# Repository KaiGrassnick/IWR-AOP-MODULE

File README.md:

# IWR-AOP-MODULE

**Revision 1.1** · KiCad 10 · six-layer, 85.6 × 33.7 mm · designed and simulated, not yet built

A self-contained 60 GHz mmWave radar module built around TI's **IWR6843AOP** (antenna-on-package). It boots its own firmware from on-board flash and connects to a PC over USB-C or a carrier through two rear sockets.

## Features

- **Radar.** IWR6843AOP: 60–64 GHz FMCW, 4 GHz continuous sweep, 3 transmitters and 4 receivers with antennas in the package, C674x DSP, hardware FFT/CFAR accelerator and Arm Cortex-R4F. Detection and tracking run on the radar; the host receives results.
- **Standalone boot.** 32 Mbit QSPI flash (`U301`, MX25L3233F).
- **USB-C.** One cable supplies power and two CP2105 serial ports: control/flashing and radar data. BOOT and RESET buttons select flashing mode.
- **Carrier.** 5 V input, UART and SPI, boot-mode select, reset, disable, interrupt, hardware frame-start pulse and frame-sync input.
- **Power.** USB-C or carrier 5 V feeds an ideal-diode OR and four-rail TI LP87524J-Q1 PMIC. The PMIC sequences the rails and regulates the 1.0 V and 1.8 V rails at the radar (remote sense). A small heat sink on the back under the radar carries the heat away. A TPS386000 supervisor holds the radar in reset until all four rails are good, and the PMIC asserts reset when the carrier disables them. The radar can reach the PMIC over I²C.
- **Debug.** Rear Cortex-10 JTAG header for development off a carrier (Black Magic Probe or XDS110), debug-boot solder jumper, and test pads for every rail, enable and reset. Flashing requires only USB and the BOOT/RESET buttons.
- **RF-ready layout.** The radar sits on the bottom edge with a notch above it, giving the 0.2 mm antenna edge gaps TI specifies. A GND pad sits under the die on both faces.

## Key specifications

| | |
|---|---|
| Supply | 5 V (4.5–5.5 V), ≥ 1.5 A source. Design estimate: about 1.2–1.3 A peak, 0.3–0.45 A average |
| USB | USB-C, default USB power (no PD), CP2105 dual UART |
| Carrier logic | 3.3 V, not 5 V tolerant |
| Carrier sockets | `J400` 2×6 (UART, control, 5 V in) and `J401` 2×5 (SPI, data); HCTL PM254, 2.54 mm, 8.5 mm |
| Mounting | Three M3 holes |
| Board | 85.6 × 33.7 mm, 6 layers, 1.6 mm, ENIG, filled and capped vias |
| Parts | 164 assembled on 46 BOM lines, both sides (`R604` and `C605` left unfitted), plus a 14 × 14 × 6 mm heat sink bonded on by hand |
| Ambient | Up to about 58 °C at 1.75 W radar power and 43 °C at 2.3 W in still air with the heat sink (model, spec §10). Target: 30 °C room temperature; in a case, the case decides the margin ([`case/`](case/README.md)) |

Full modes, rails, boot, mechanics, stackup and firmware requirements: **[hardware specification](docs/STG-HW-SPEC-004_IWR-AOP-MODULE.md)**. Enclosure design: [case notes](case/README.md).

## Using it

Use USB-C or a carrier, never both: they share the radar's control UART.

### USB-C

Power from a USB-C port or charger offering at least 1.5 A (default USB power, no PD). USB-A-to-C cables and 500/900 mA ports can brown out during chirps. The CP2105 bridge enumerates as two COM ports:

| Channel | COM port | Radar side | Direction | Use |
|---|---|---|---|---|
| Control | *Enhanced* (ECI) | UARTA | Both | Commands, configuration, UART flashing |
| Data | *Standard* (SCI) | UARTB TX | Radar → PC | Data stream |

| Action | How |
|---|---|
| Reset | Press RESET |
| Flash | Hold RESET, hold BOOT, release RESET, release BOOT; program over the Enhanced port; press RESET to boot from flash |
| JTAG | `J301` Cortex-10 header (1.27 mm); bridge `JP300` for debug boot (spec §4.3) |

### Carrier

Power from one regulated 5 V supply (4.5–5.5 V, ≥ 1.5 A) on `J400.11/.12`, with USB unplugged. All logic is 3.3 V and not 5 V tolerant. A carrier can talk to the radar three ways:

| Channel | Radar side | Pins | Direction | Use |
|---|---|---|---|---|
| Control UART | UARTA | TX `J400.1`, RX `J400.2` | Both | Commands, configuration, UART flashing (same UART as the USB Enhanced port) |
| Data UART | UARTB TX | `J401.9` | Radar → carrier | Data stream (same as the USB Standard port) |
| SPI | SPIA, radar is peripheral | CLK `J401.1`, MOSI `J401.3`, MISO `J401.4`, CS `J401.5`; IRQ `J401.7` | Both | Protocol set by the radar firmware |

Control and timing signals:

| Signal | Pin | Direction | Function |
|---|---|---|---|
| `HOST_NRESET` | `J400.8` | Open-drain, both | Pull low to reset. High means rails good and reset released |
| `HOST_DISABLE` | `J400.7` | In, active high | High turns off every radar rail |
| `AOP_SOP2` | `J400.5` | In | Boot select: high during reset enters UART flashing |
| `AOP_NERROR_OUT` | `J400.6` | Out, open-drain | Radar error flag (optional) |
| `HOST_SYNC_IN` | `J400.3` | In | Frame trigger, 25 ns–4 µs pulse (optional) |
| `FRAME_START` | `J401.8` | Out | Frame-start pulse (optional) |

To flash from a carrier: hold `J400.5` high, pulse `J400.8` low, program over the control UART, release `J400.5` and reset again.

Carrier rules (spec §5):

- Keep every carrier output and pull-up high-impedance until `J400.8` first goes high, and while `HOST_DISABLE` is asserted.
- Reset only by pulling `J400.8` low open-drain; never drive it high.

## Pinout

Back view: `J400` is on the left and `J401` on the right.

Full pin directions and carrier rules: spec §5.

## Mechanical

Back view, mm. Everything is symmetric about the board centrelines (℄). Sockets sit on the hole columns, centred vertically. Keep carrier metal out of the antenna aperture (spec §6). For CAD work use the board STEP, [`docs/3d/IWR-AOP-MODULE.step`](docs/3d/IWR-AOP-MODULE.step) (origin at the outline's top-left corner); window and heat-path rules for a case are in [`case/`](case/README.md).

## Cost

Parts for one board cost about $37.60 at LCSC list prices for a single board and $33.10 each for 30 (15 November 2026); the IWR6843AOP is about $19.50 of that. Per-part prices are in [docs/bom-cost.csv](docs/bom-cost.csv), rebuilt by `tools/bom_cost.py`. The bare PCB, JLCPCB's assembly fees and the heat sink (bought separately, a few dollars) come on top; JLCPCB quotes those at order time.

## Repository layout

```
IWR-AOP-MODULE.kicad_pro / .kicad_sch / .kicad_pcb / .kicad_dru   KiCad 10 project, design rules
IWR-AOP-MODULE.kicad_sch   Power entry, LM66200 source OR, enable, integration notes
rails.kicad_sch        LP87524J-Q1 PMIC, four radar rails, reset, test pads
aop.kicad_sch          IWR6843AOP, crystal, boot flash, straps, JTAG
interfaces.kicad_sch   USB-C, CP2105 dual UART, J400 / J401 sockets, buttons
libraries/             Project symbols, footprints and STEP 3D models (IWR-AOP-MODULE.*)
                       Sockets, JTAG header, buttons and LP87524J: LCSC/EasyEDA models fitted
                       to the pads; U200: KiCad's 4x4 QFN-24 model
docs/                  Hardware specification and BOM cost
  images/              Board renders, orbit GIF, pinout.svg and dimensions.svg
  videos/              IWR-AOP-MODULE-orbit.mp4
  3d/                  Board STEP (origin: outline top-left)
tools/
  board_svg.py         Pinout and dimension SVG generation
  render/              Blender product renders and orbit video pipeline
  rev11/               Scripts that generate the schematic and layout changes of revision 1.1
  bom_cost.py          Rebuilds docs/bom-cost.csv from current LCSC prices
  heatsink_model.py    STEP model of heat sink HS300 (CadQuery)
simulation/            Netlist checks, post-layout extraction, ngspice and thermal models, results
cosim/                 Firmware running on a model of the board, chirp load replayed in ngspice
manufacturing/         JLCPCB package builder and output (jlcpcb/)
case/                  Notes for the enclosure design: heat path, antenna window, geometry
references/            Datasheets and JLC's sample BOM format
CHANGELOG.md           Release history
LICENSE                MIT license
build/                 Generated outputs (gitignored)
```

The project is self-contained: everything outside the stock KiCad 10 libraries is in `libraries/`.

## Status

**Designed and simulated, not yet built.** The board is fully routed. ERC has no errors; DRC reports 0 unconnected and 0 schematic-parity issues, plus 53 accepted findings (spec §7.3). Post-layout extraction and simulation cover rail voltages at the radar balls, sequencing and reset, loop stability, chirp load steps, ripple, USB hot plug and temperature: see [`simulation/`](simulation/README.md). Test firmware runs on a model of the board in [`cosim/`](cosim/README.md): power-up, flashing, resets, the PMIC trim over I²C (limited to 1000–1005 mV), a thermal governor that throttles from 90 °C and stops at 100 °C, and host settings with compiled-in limits. Three TX in one chirp is off by default because it does not fit the 1.0 V window in the replay. Enclosure requirements (heat path, antenna window, keep-outs) are in [`case/`](case/README.md). Operating conditions and the basis of the models are in spec §10 and the measurements for the first boards in spec §9.

## License

MIT — see [LICENSE](LICENSE).

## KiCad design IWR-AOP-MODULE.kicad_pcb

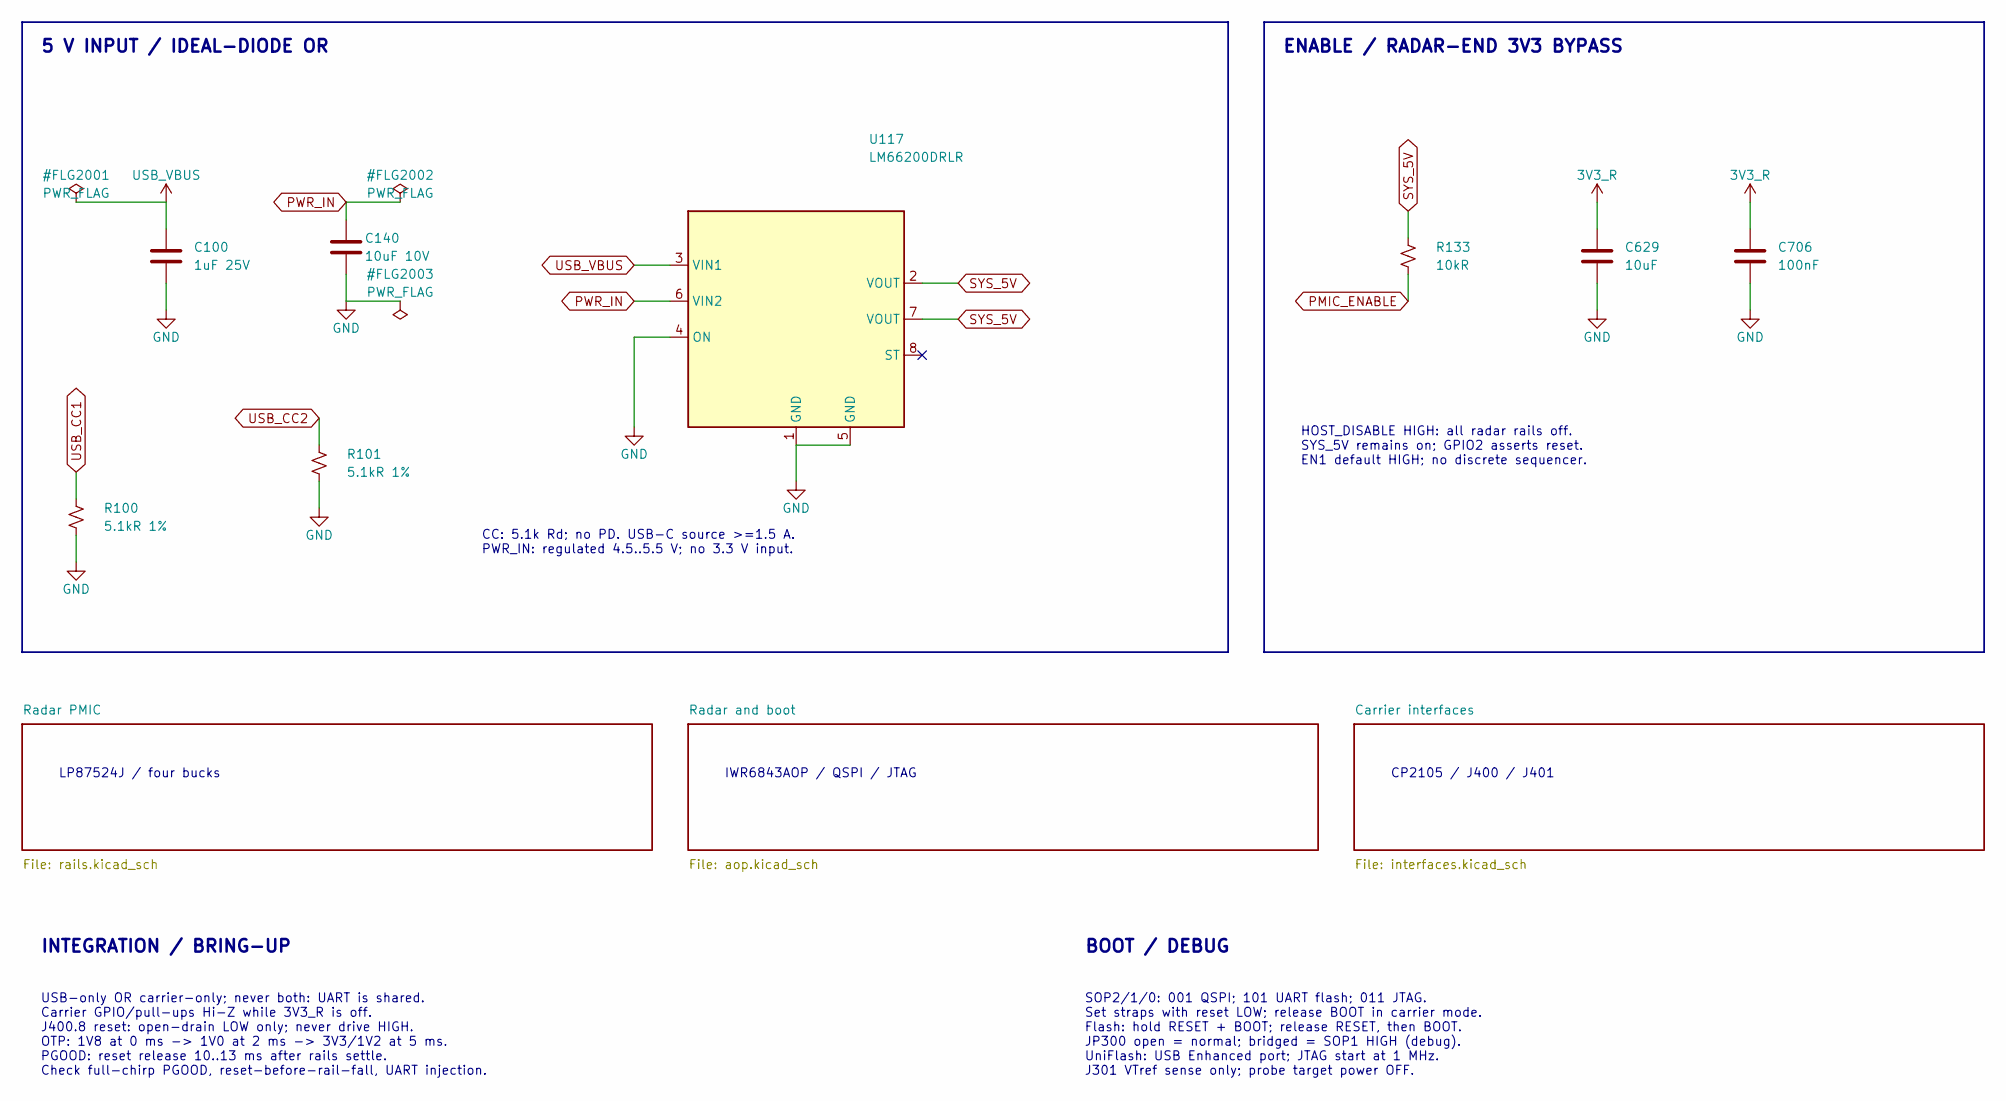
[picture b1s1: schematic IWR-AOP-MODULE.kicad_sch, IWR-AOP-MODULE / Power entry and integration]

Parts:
C100: 1uF 25V; C_0805_2012Metric; MPN CL21B105KBFNNNE; LCSC C28323
C140: 10uF 10V; C_0805_2012Metric; MPN GRM21BR71A106KE51L; LCSC C86038
C629: 10uF; C_0805_2012Metric; Tolerance 10%; Rating X7R 10V; MPN GRM21BR71A106KE51L; LCSC C86038
C706: 100nF; C_0402_1005Metric; MPN CL05B104KO5NNNC; LCSC C1525
R100, R101: 5.1kR 1%; R_0402_1005Metric; MPN 0402WGF5101TCE; LCSC C25905
R133: 10kR; R_0402_1005Metric; MPN 0402WGF1002TCE; LCSC C25744
U117: LM66200DRLR; SOT-583-8; MPN LM66200DRLR; LCSC C3235556

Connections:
3V3_R: C629.1, C706.1; also elsewhere on the board
GND: C100.2, C140.2, C629.2, C706.2, R100.2, R101.2, U117.1 (GND), U117.4 (ON), U117.5 (GND); also elsewhere on the board
PMIC_ENABLE: R133.2; also elsewhere on the board
PWR_IN: C140.1, U117.6 (VIN2); also elsewhere on the board
SYS_5V: R133.1, U117.2 (VOUT), U117.7 (VOUT); also elsewhere on the board
USB_CC1: R100.1; also elsewhere on the board
USB_CC2: R101.1; also elsewhere on the board
USB_VBUS: C100.1, U117.3 (VIN1); also elsewhere on the board

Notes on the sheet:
5 V INPUT / IDEAL-DIODE OR
CC: 5.1k Rd; no PD. USB-C source >=1.5 A. PWR_IN: regulated 4.5..5.5 V; no 3.3 V input.
ENABLE / RADAR-END 3V3 BYPASS
HOST_DISABLE HIGH: all radar rails off. SYS_5V remains on; GPIO2 asserts reset. EN1 default HIGH; no discrete sequencer.
LP87524J / four bucks
IWR6843AOP / QSPI / JTAG
CP2105 / J400 / J401
INTEGRATION / BRING-UP
USB-only OR carrier-only; never both: UART is shared. Carrier GPIO/pull-ups Hi-Z while 3V3_R is off. J400.8 reset: open-drain LOW only; never drive HIGH. OTP: 1V8 at 0 ms -> 1V0 at 2 ms -> 3V3/1V2 at 5 ms. PGOOD: reset release 10..13 ms after rails settle. Check full-chirp PGOOD, reset-before-rail-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
BOOT / DEBUG
SOP2/1/0: 001 QSPI; 101 UART flash; 011 JTAG. Set straps with reset LOW; release BOOT in carrier mode. Flash: hold RESET + BOOT; release RESET, then BOOT. JP300 open = normal; bridged = SOP1 HIGH (debug). UniFlash: USB Enhanced port; JTAG start at 1 MHz. J301 VTref sense only; probe target power OF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

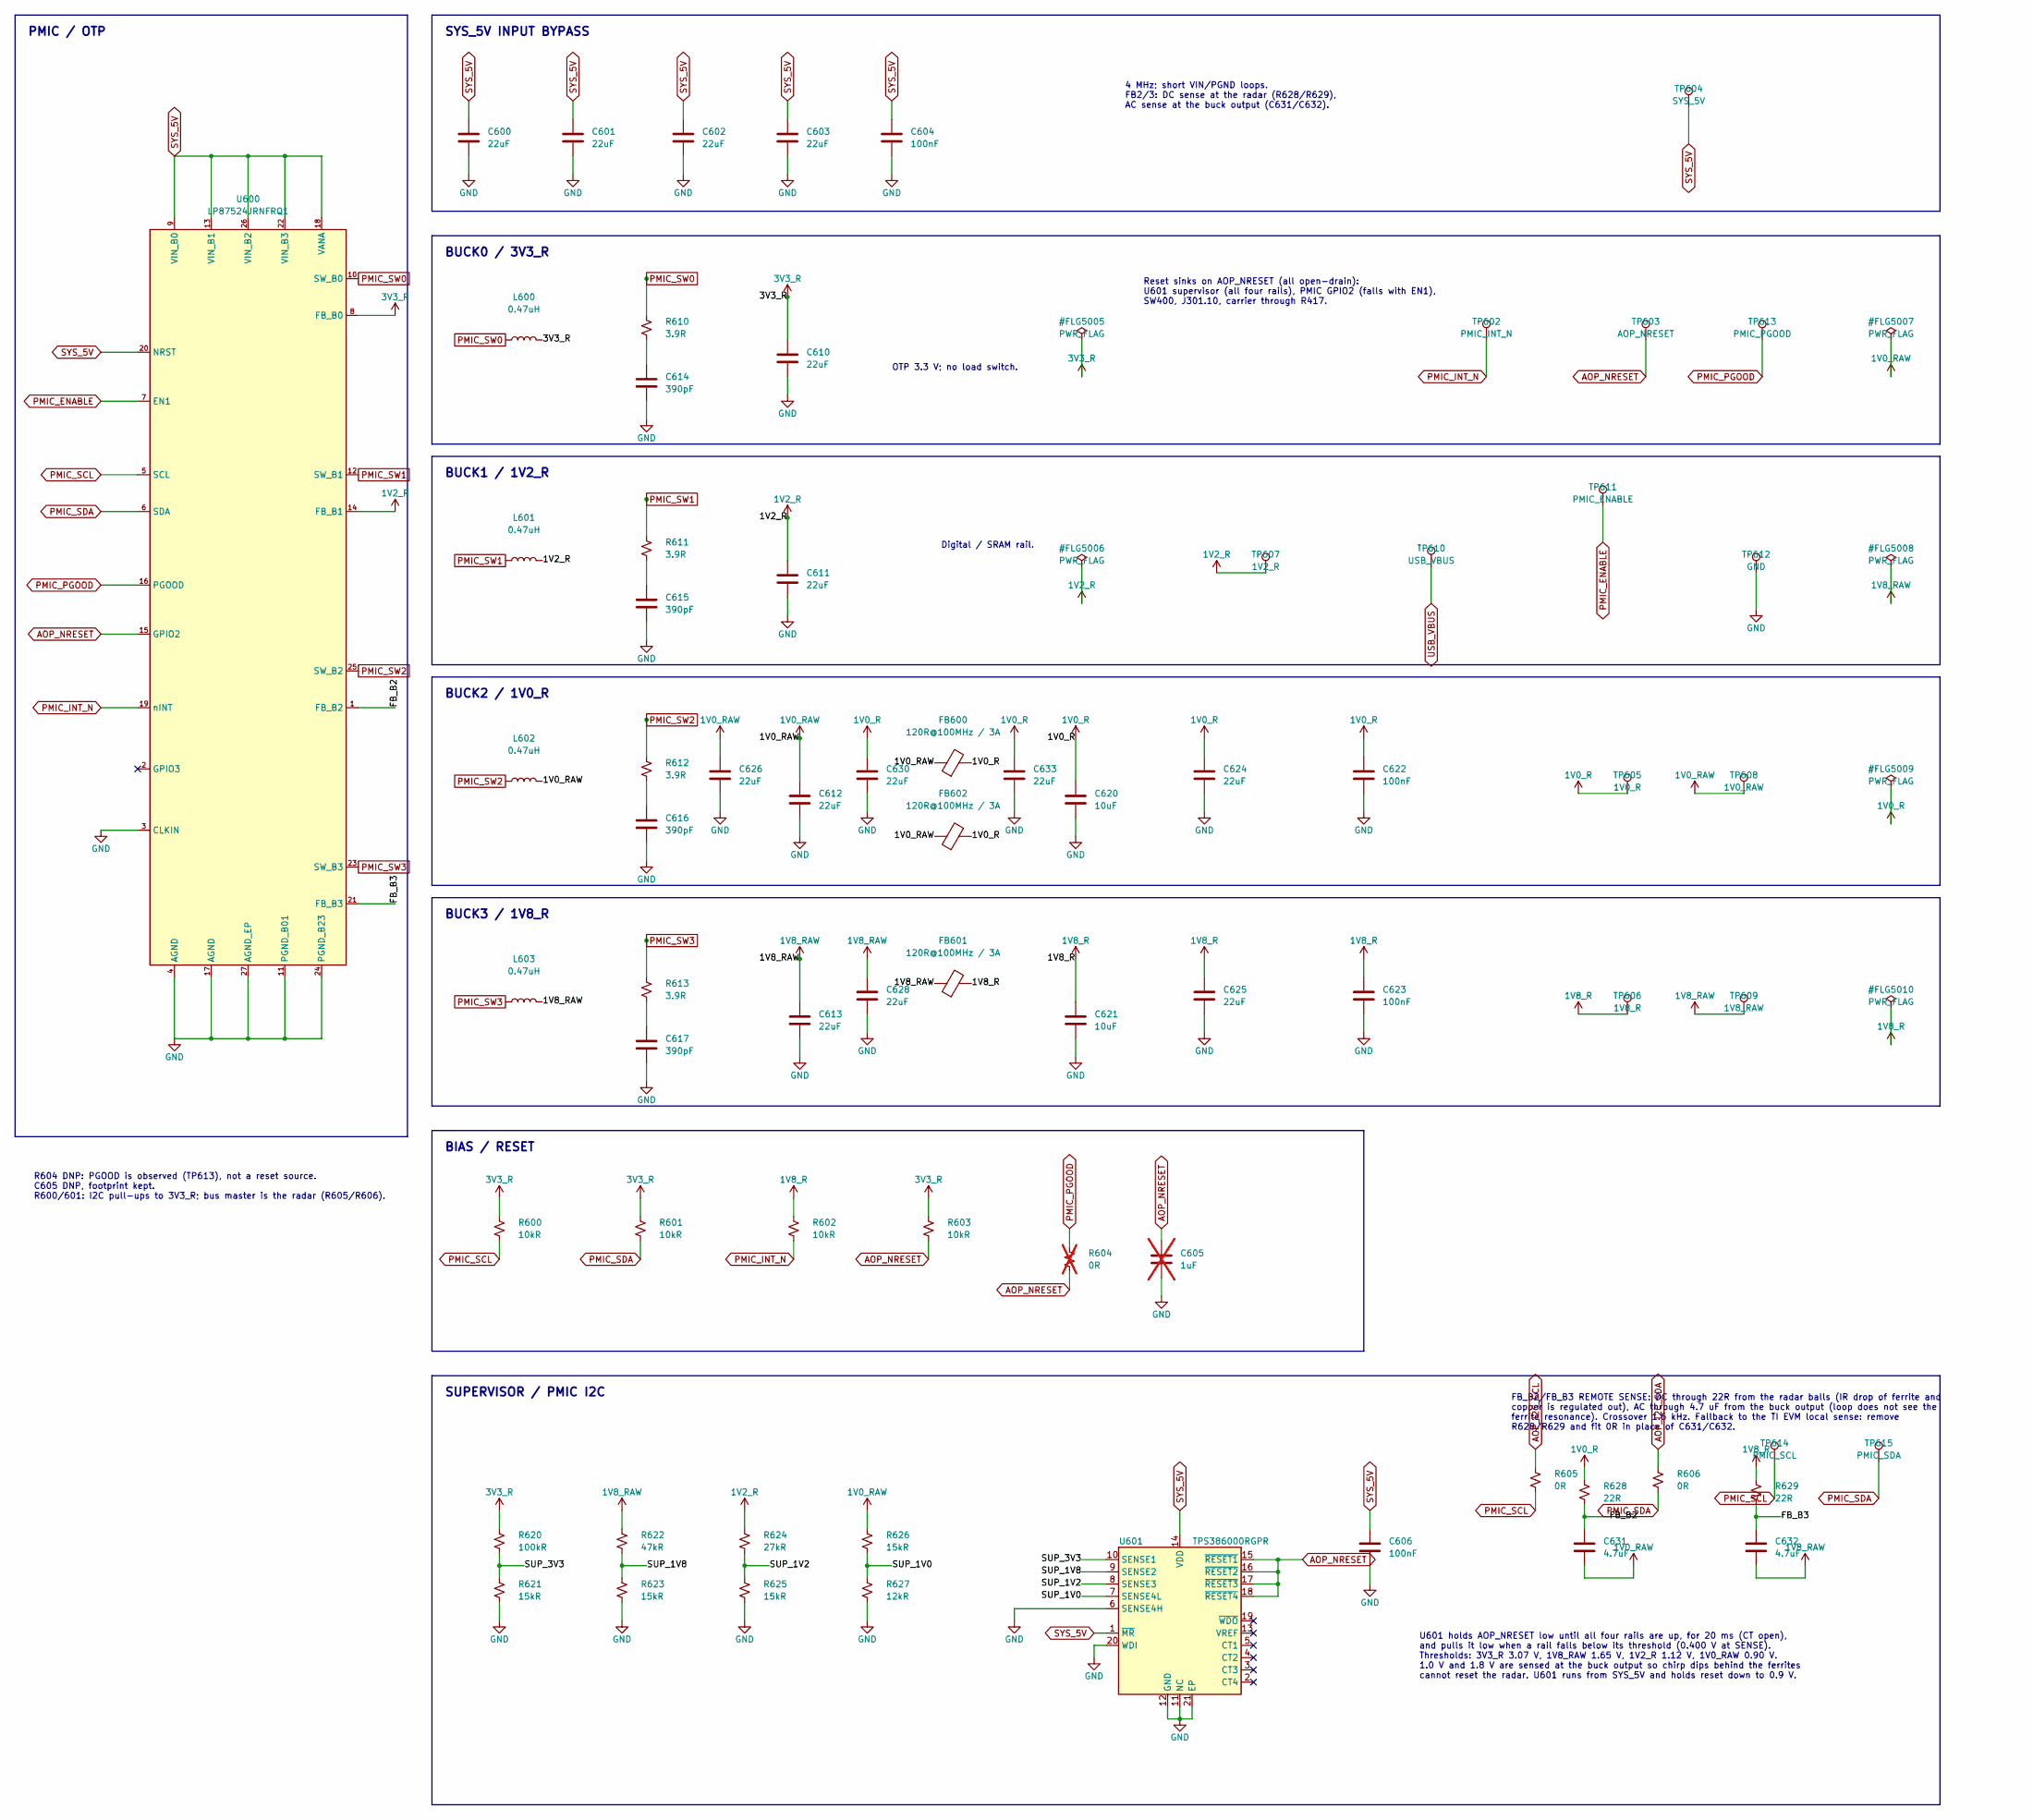
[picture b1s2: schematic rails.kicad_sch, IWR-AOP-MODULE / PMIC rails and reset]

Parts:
C600, C601, C602, C603, C610, C611, C612, C613: 22uF; C_1210_3225Metric; Rating X7R 25V; Tolerance 10%; MPN GRM32ER71E226KE15L; LCSC C21397
C604, C606, C622, C623: 100nF; C_0402_1005Metric; MPN CL05B104KO5NNNC; LCSC C1525
C605: 1uF; C_0603_1608Metric; MPN CL10A105KB8NNNC; LCSC C15849; not fitted
C614, C615, C616, C617: 390pF; C_0402_1005Metric; Tolerance 5%; Rating C0G 50V; MPN GRM1555C1H391JA01D; LCSC C76967
C620, C621: 10uF; C_0805_2012Metric; Tolerance 10%; Rating X7R 10V; MPN GRM21BR71A106KE51L; LCSC C86038
C624, C625, C626, C628, C630, C633: 22uF; C_0805_2012Metric; Rating X5R 25V; Tolerance 20%; MPN CL21A226MAQNNNE; LCSC C45783
C631, C632: 4.7uF; C_0603_1608Metric; Rating X5R 16V; MPN CL10A475KO8NNNC; LCSC C19666
FB600, FB601, FB602: 120R@100MHz / 3A; L_0603_1608Metric; MPN BLM18KG121TH1D; LCSC C437404
L600, L601, L602, L603: 0.47uH; L_Sunlord_MWSA0402S; MPN MWSA0402S-R47MT; LCSC C6331050
R600, R601, R602, R603: 10kR; R_0402_1005Metric; MPN 0402WGF1002TCE; LCSC C25744
R604: 0R; R_0402_1005Metric; MPN 0402WGF0000TCE; LCSC C17168; not fitted
R605, R606: 0R; R_0402_1005Metric; MPN 0402WGF0000TCE; LCSC C17168
R610, R611, R612, R613: 3.9R; R_0603_1608Metric; Tolerance 1%; Rating 100mW; MPN RC0603FR-073R9L; LCSC C482845
R620: 100kR; R_0402_1005Metric; MPN 0402WGF1003TCE; LCSC C25741
R621, R623, R625, R626: 15kR; R_0402_1005Metric; MPN 0402WGF1502TCE; LCSC C25756
R622: 47kR; R_0402_1005Metric; MPN 0402WGF4702TCE; LCSC C25792
R624: 27kR; R_0402_1005Metric; MPN 0402WGF2702TCE; LCSC C25771
R627: 12kR; R_0402_1005Metric; MPN 0402WGF1202TCE; LCSC C25752
R628, R629: 22R; R_0402_1005Metric; MPN 0402WGF220JTCE; LCSC C25092
TP602: PMIC_INT_N; TestPoint_Pad_D1.0mm; MPN PCB_TEST_PAD_1MM
TP603: AOP_NRESET; TestPoint_Pad_D1.0mm; MPN PCB_TEST_PAD_1MM
TP604: SYS_5V; TestPoint_Pad_D1.0mm; MPN PCB_TEST_PAD_1MM
TP605: 1V0_R; TestPoint_Pad_D1.0mm; MPN PCB_TEST_PAD_1MM
TP606: 1V8_R; TestPoint_Pad_D1.0mm; MPN PCB_TEST_PAD_1MM
TP607: 1V2_R; TestPoint_Pad_D1.0mm; MPN PCB_TEST_PAD_1MM
TP608: 1V0_RAW; TestPoint_Pad_D1.0mm; MPN PCB_TEST_PAD_1MM
TP609: 1V8_RAW; TestPoint_Pad_D1.0mm; MPN PCB_TEST_PAD_1MM
TP610: USB_VBUS; TestPoint_Pad_D1.0mm; MPN PCB_TEST_PAD_1MM
TP611: PMIC_ENABLE; TestPoint_Pad_D1.0mm; MPN PCB_TEST_PAD_1MM
TP612: GND; TestPoint_Pad_D1.0mm; MPN PCB_TEST_PAD_1MM
TP613: PMIC_PGOOD; TestPoint_Pad_D1.0mm; MPN PCB_TEST_PAD_1MM
TP614: PMIC_SCL; TestPoint_Pad_D1.0mm; MPN PCB_TEST_PAD_1MM
TP615: PMIC_SDA; TestPoint_Pad_D1.0mm; MPN PCB_TEST_PAD_1MM
U600: LP87524JRNFRQ1; Texas_RNF0026C_LP87524J; MPN LP87524JRNFRQ1; LCSC C701982
U601: TPS386000RGPR; Texas_RGP0020D_VQFN-20-1EP_4x4mm_P0.5mm_EP2.7x2.7mm; MPN TPS386000RGPR; LCSC C702221

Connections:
1V0_R: C620.1, C622.1, C624.1, C630.1, C633.1, FB600.2, FB602.2, R628.1, TP605.1; also elsewhere on the board
1V0_RAW: C612.1, C626.1, C631.2, FB600.1, FB602.1, L602.2, R626.1, TP608.1
1V2_R: C611.1, L601.2, R624.1, TP607.1, U600.14 (FB_B1); also elsewhere on the board
1V8_R: C621.1, C623.1, C625.1, FB601.2, R602.1, R629.1, TP606.1; also elsewhere on the board
1V8_RAW: C613.1, C628.1, C632.2, FB601.1, L603.2, R622.1, TP609.1
3V3_R: C610.1, L600.2, R600.1, R601.1, R603.1, R620.1, U600.8 (FB_B0); also elsewhere on the board
/Radar PMIC/FB_B2: C631.1, R628.2, U600.1 (FB_B2)
/Radar PMIC/FB_B3: C632.1, R629.2, U600.21 (FB_B3)
/Radar PMIC/SUP_1V0: R626.2, R627.1, U601.7 (SENSE4L)
/Radar PMIC/SUP_1V2: R624.2, R625.1, U601.8 (SENSE3)
/Radar PMIC/SUP_1V8: R622.2, R623.1, U601.9 (SENSE2)
/Radar PMIC/SUP_3V3: R620.2, R621.1, U601.10 (SENSE1)
AOP_I2C_SCL: R605.1; also elsewhere on the board
AOP_I2C_SDA: R606.1; also elsewhere on the board
AOP_NRESET: C605.1, R603.2, R604.2, TP603.1 (1_1), U600.15 (GPIO2), U601.15 (~RESET1), U601.16 (~RESET2), U601.17 (~RESET3), U601.18 (~RESET4); also elsewhere on the board
GND: C600.2, C601.2, C602.2, C603.2, C604.2, C605.2, C606.2, C610.2, C611.2, C612.2, C613.2, C614.2, C615.2, C616.2, C617.2, C620.2, C621.2, C622.2, C623.2, C624.2, C625.2, C626.2, C628.2, C630.2, C633.2, R621.2, R623.2, R625.2, R627.2, TP612.1, U600.3 (CLKIN), U600.4 (AGND), U600.11 (PGND_B01), U600.17 (AGND), U600.24 (PGND_B23), U600.27 (AGND_EP), U601.6 (SENSE4H), U601.11 (NC), U601.12 (GND), U601.20 (WDI), U601.21 (EP); also elsewhere on the board
unnamed: C614.1, R610.2
unnamed: C615.1, R611.2
unnamed: C616.1, R612.2
unnamed: C617.1, R613.2
PMIC_ENABLE: TP611.1, U600.7 (EN1); also elsewhere on the board
PMIC_INT_N: R602.2, TP602.1 (1_1), U600.19 (nINT)
PMIC_PGOOD: R604.1, TP613.1, U600.16 (PGOOD)
PMIC_SCL: R600.2, R605.2, TP614.1, U600.5 (SCL)
PMIC_SDA: R601.2, R606.2, TP615.1, U600.6 (SDA)
PMIC_SW0: L600.1, R610.1, U600.10 (SW_B0)
PMIC_SW1: L601.1, R611.1, U600.12 (SW_B1)
PMIC_SW2: L602.1, R612.1, U600.25 (SW_B2)
PMIC_SW3: L603.1, R613.1, U600.23 (SW_B3)
SYS_5V: C600.1, C601.1, C602.1, C603.1, C604.1, C606.1, TP604.1, U600.9 (VIN_B0), U600.13 (VIN_B1), U600.18 (VANA), U600.20 (NRST), U600.22 (VIN_B3), U600.26 (VIN_B2), U601.1 (~MR), U601.14 (VDD); also elsewhere on the board
USB_VBUS: TP610.1; also elsewhere on the board

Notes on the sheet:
PMIC / OTP
SYS_5V INPUT BYPASS
4 MHz; short VIN/PGND loops. FB2/3: DC sense at the radar (R628/R629), AC sense at the buck output (C631/C632).
BUCK0 / 3V3_R
OTP 3.3 V; no load switch.
BUCK1 / 1V2_R
Digital / SRAM rail.
BUCK2 / 1V0_R
BUCK3 / 1V8_R
BIAS / RESET
R604 DNP: PGOOD is observed (TP613), not a reset source. C605 DNP, footprint kept. R600/601: I2C pull-ups to 3V3_R; bus master is the radar (R605/R606).
SUPERVISOR / PMIC I2C
U601 holds AOP_NRESET low until all four rails are up, for 20 ms (CT open), and pulls it low when a rail falls below its threshold (0.400 V at SENSE). Thresholds: 3V3_R 3.07 V, 1V8_RAW 1.65 V, 1V2_R 1.12 V, 1V0_RAW 0.90 V. 1.0 V and 1.8 V are sensed at the buck output so chirp dips behind the ferri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
FB_B2/FB_B3 REMOTE SENSE: DC through 22R from the radar balls (IR drop of ferrite and copper is regulated out), AC through 4.7 uF from the buck output (loop does not see the ferrite resonance). Crossover 1.6 kHz. Fallback to the TI EVM local sense: remove R628/R629 and fit 0R in place of C631/C632.
Reset sinks on AOP_NRESET (all open-drain): U601 supervisor (all four rails), PMIC GPIO2 (falls with EN1), SW400, J301.10, carrier through R417.

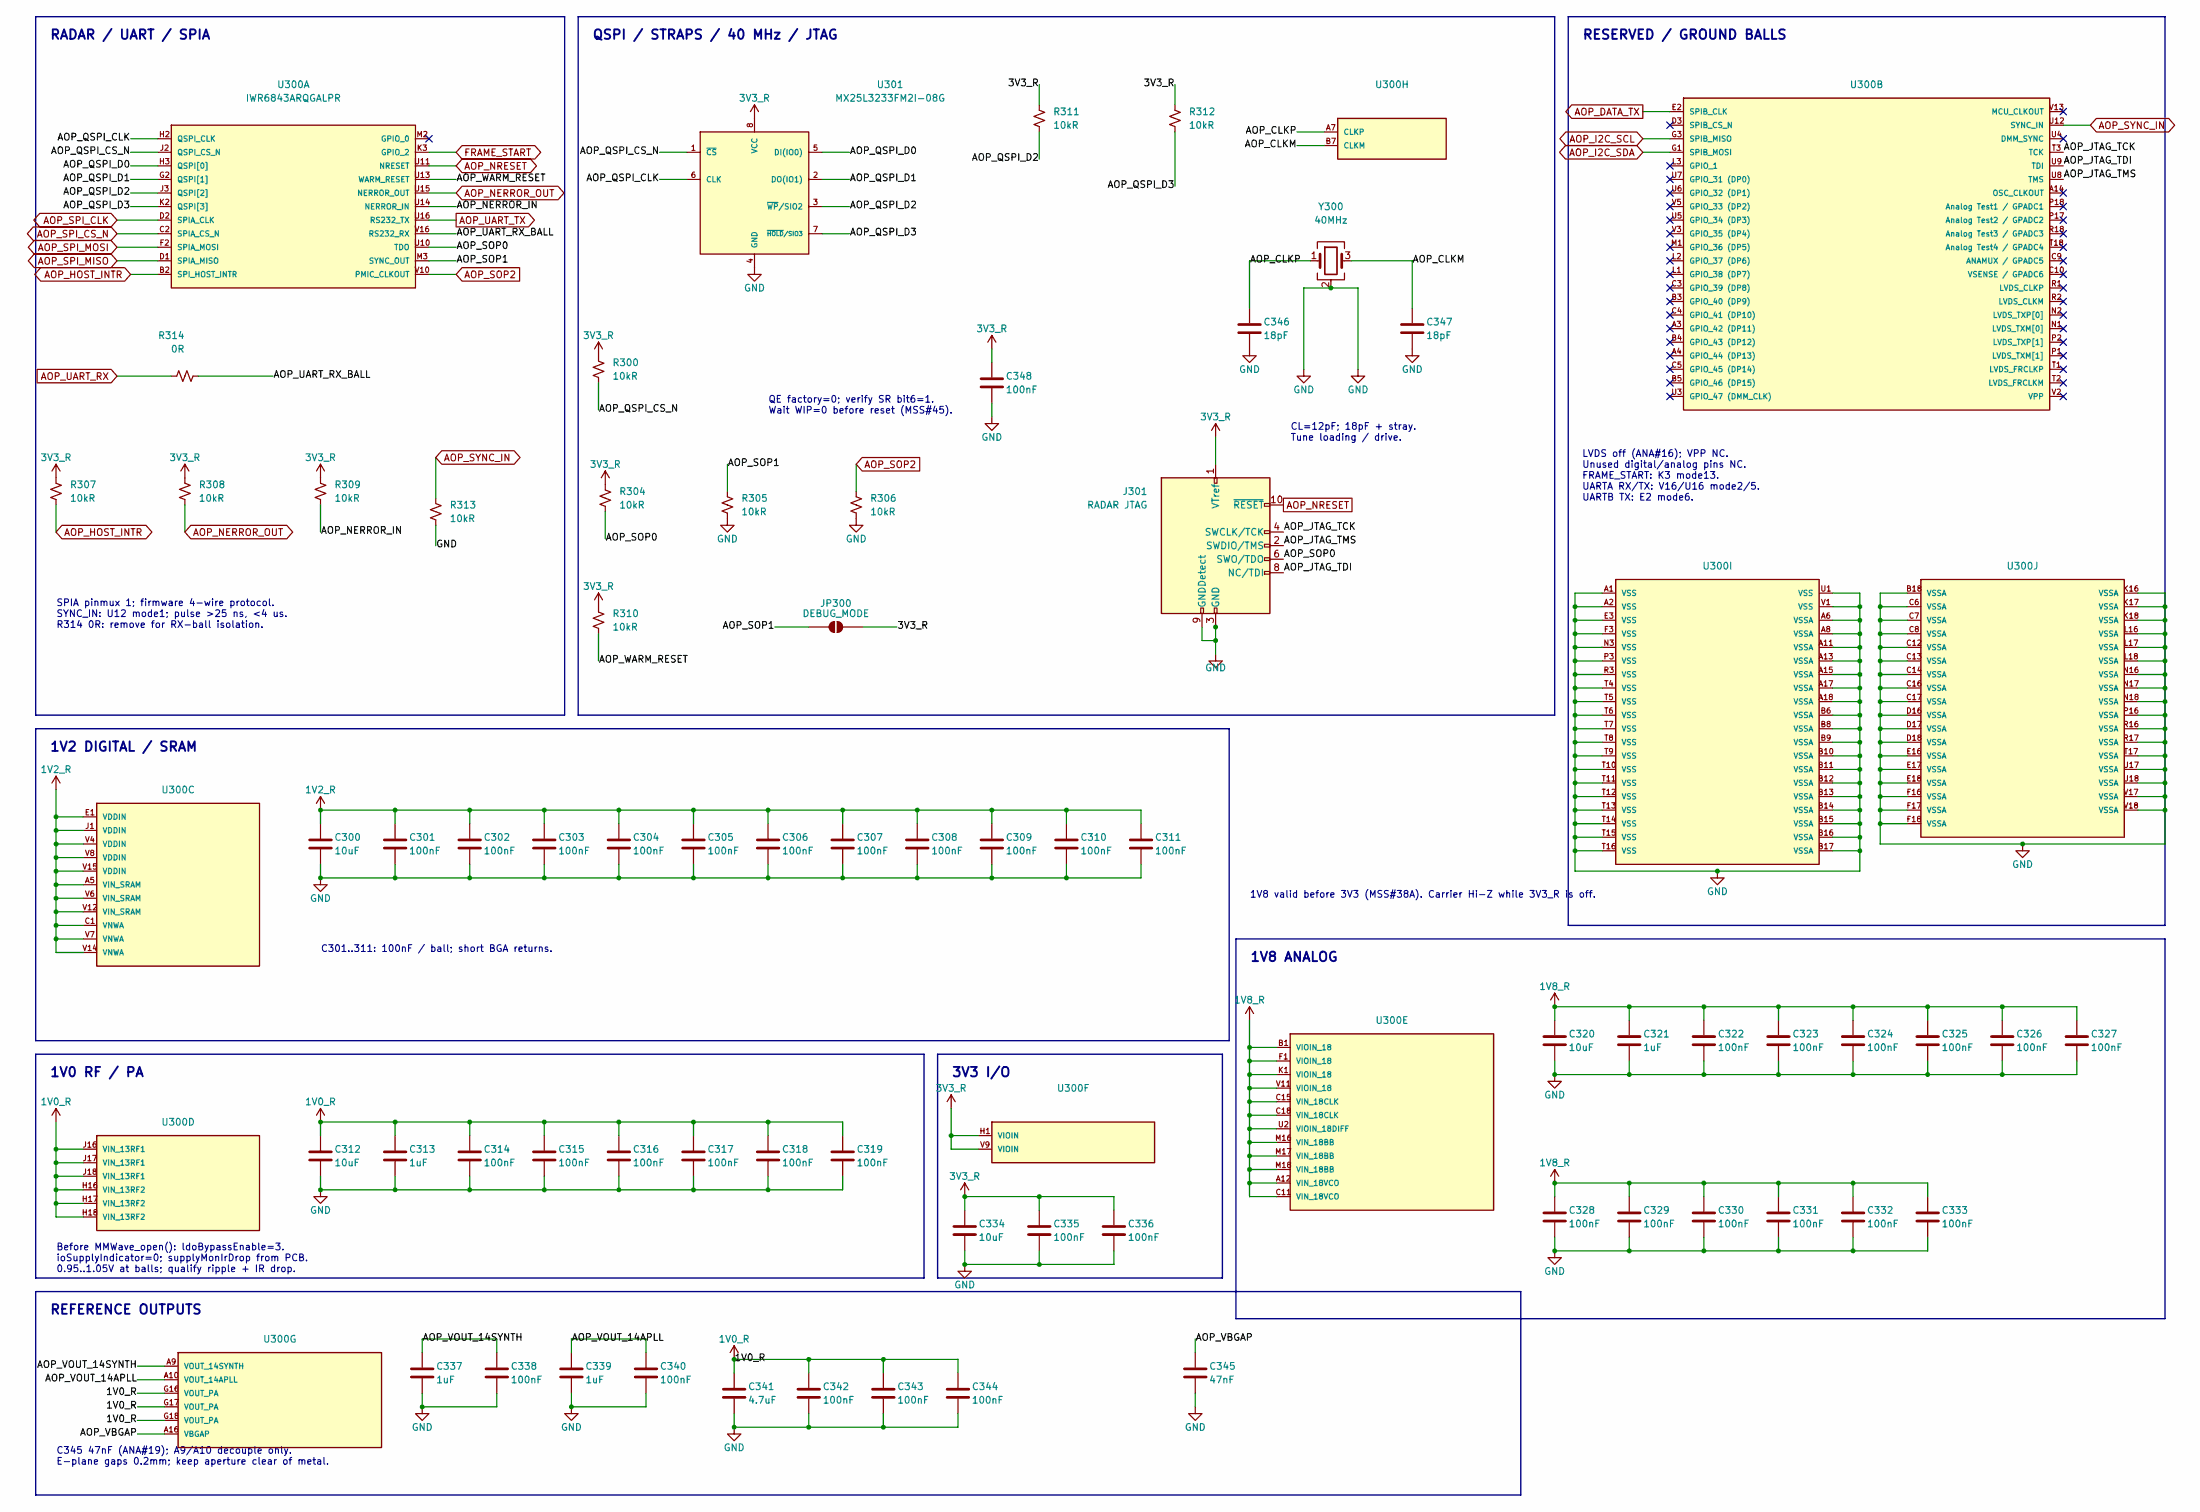
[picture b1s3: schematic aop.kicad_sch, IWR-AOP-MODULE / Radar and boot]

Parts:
C300, C312, C320, C334: 10uF; C_0805_2012Metric; MPN CL21A106KAYNNNE; LCSC C15850
C301, C302, C303, C304, C305, C306, C307, C308, C309, C310, C311, C314, C315, C316, C317, C318, C319, C322, C323, C324, C325, C326, C327, C328, C329, C330, C331, C332, C333, C335, C336, C338, C340, C342, C343, C344, C348: 100nF; C_0402_1005Metric; MPN CL05B104KO5NNNC; LCSC C1525
C313, C321, C337, C339: 1uF; C_0603_1608Metric; MPN CL10A105KB8NNNC; LCSC C15849
C341: 4.7uF; C_0603_1608Metric; MPN CL10A475KO8NNNC; LCSC C19666
C345: 47nF; C_0402_1005Metric; MPN GRM155R71E473KA88D; LCSC C77017
C346, C347: 18pF; C_0402_1005Metric; MPN 0402CG180J500NT; LCSC C1549
J301: RADAR JTAG; XKB_X1270WVS-2x05B-9TV01_2x05_P1.27mm_Vertical; MPN X1270WVS-2x05B-9TV01; LCSC C2962219
JP300: DEBUG_MODE; SolderJumper-2_P1.3mm_Open_RoundedPad1.0x1.5mm
R300, R304, R305, R306, R307, R308, R309, R310, R311, R312, R313: 10kR; R_0402_1005Metric; MPN 0402WGF1002TCE; LCSC C25744
R314: 0R; R_0402_1005Metric; MPN 0402WGF0000TCE; LCSC C17168
U300: IWR6843ARQGALPR; BGA180C80P18X18_1500X1500X97N; MPN IWR6843ARQGALPR; LCSC C2871887
U301: MX25L3233FM2I-08G; SOIC-8_5.3x5.3mm_P1.27mm; MPN MX25L3233FM2I-08G; LCSC C190802
Y300: 40MHz; Crystal_SMD_3225-4Pin_3.2x2.5mm; MPN XL2EL89COI-111YLC-40M; LCSC C18214314

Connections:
1V0_R: C312.1, C313.1, C314.1, C315.1, C316.1, C317.1, C318.1, C319.1, C341.1, C342.1, C343.1, C344.1, U300.G16 (VOUT_PA), U300.G17 (VOUT_PA), U300.G18 (VOUT_PA), U300.H16 (VIN_13RF2), U300.H17 (VIN_13RF2), U300.H18 (VIN_13RF2), U300.J16 (VIN_13RF1), U300.J17 (VIN_13RF1), U300.J18 (VIN_13RF1); also elsewhere on the board
1V2_R: C300.1, C301.1, C302.1, C303.1, C304.1, C305.1, C306.1, C307.1, C308.1, C309.1, C310.1, C311.1, U300.A5 (VIN_SRAM), U300.C1 (VNWA), U300.E1 (VDDIN), U300.J1 (VDDIN), U300.V4 (VDDIN), U300.V6 (VIN_SRAM), U300.V7 (VNWA), U300.V8 (VDDIN), U300.V12 (VIN_SRAM), U300.V14 (VNWA), U300.V15 (VDDIN); also elsewhere on the board
1V8_R: C320.1, C321.1, C322.1, C323.1, C324.1, C325.1, C326.1, C327.1, C328.1, C329.1, C330.1, C331.1, C332.1, C333.1, U300.A12 (VIN_18VCO), U300.B1 (VIOIN_18), U300.C11 (VIN_18VCO), U300.C15 (VIN_18CLK), U300.C18 (VIN_18CLK), U300.F1 (VIOIN_18), U300.K1 (VIOIN_18), U300.M16 (VIN_18BB), U300.M17 (VIN_18BB), U300.M18 (VIN_18BB), U300.U2 (VIOIN_18DIFF), U300.V11 (VIOIN_18); also elsewhere on the board
3V3_R: C334.1, C335.1, C336.1, C348.1, J301.1 (VTref), JP300.2 (B), R300.1, R304.1, R307.1, R308.1, R309.1, R310.1, R311.1, R312.1, U300.H1 (VIOIN), U300.V9 (VIOIN), U301.8 (VCC); also elsewhere on the board
/Radar and boot/AOP_CLKM: C347.1, U300.B7 (CLKM), Y300.3
/Radar and boot/AOP_CLKP: C346.1, U300.A7 (CLKP), Y300.1
/Radar and boot/AOP_JTAG_TCK: J301.4 (SWCLK/TCK), U300.T3 (TCK)
/Radar and boot/AOP_JTAG_TDI: J301.8 (NC/TDI), U300.U9 (TDI)
/Radar and boot/AOP_JTAG_TMS: J301.2 (SWDIO/TMS), U300.U8 (TMS)
/Radar and boot/AOP_NERROR_IN: R309.2, U300.U14 (NERROR_IN)
/Radar and boot/AOP_QSPI_CLK: U300.H2 (QSPI_CLK), U301.6 (CLK)
/Radar and boot/AOP_QSPI_CS_N: R300.2, U300.J2 (QSPI_CS_N), U301.1 (~CS)
/Radar and boot/AOP_QSPI_D0: U300.H3 (QSPI[0]), U301.5 (DI(IO0))
/Radar and boot/AOP_QSPI_D1: U300.G2 (QSPI[1]), U301.2 (DO(IO1))
/Radar and boot/AOP_QSPI_D2: R311.2, U300.J3 (QSPI[2]), U301.3 (~WP/SIO2)
/Radar and boot/AOP_QSPI_D3: R312.2, U300.K2 (QSPI[3]), U301.7 (~HOLD/SIO3)
/Radar and boot/AOP_SOP0: J301.6 (SWO/TDO), R304.2, U300.U10 (TDO)
/Radar and boot/AOP_SOP1: JP300.1 (A), R305.1, U300.M3 (SYNC_OUT)
/Radar and boot/AOP_UART_RX_BALL: R314.2, U300.V16 (RS232_RX)
/Radar and boot/AOP_VBGAP: C345.1, U300.A16 (VBGAP)
/Radar and boot/AOP_VOUT_14APLL: C339.1, C340.1, U300.A10 (VOUT_14APLL)
/Radar and boot/AOP_VOUT_14SYNTH: C337.1, C338.1, U300.A9 (VOUT_14SYNTH)
/Radar and boot/AOP_WARM_RESET: R310.2, U300.U13 (WARM_RESET)
AOP_DATA_TX: U300.E2 (SPIB_CLK); also elsewhere on the board
AOP_HOST_INTR: R307.2, U300.B2 (SPI_HOST_INTR); also elsewhere on the board
AOP_I2C_SCL: U300.G3 (SPIB_MISO); also elsewhere on the board
AOP_I2C_SDA: U300.G1 (SPIB_MOSI); also elsewhere on the board
AOP_NERROR_OUT: R308.2, U300.U15 (NERROR_OUT); also elsewhere on the board
AOP_NRESET: J301.10 (~RESET), U300.U11 (NRESET); also elsewhere on the board
AOP_SOP2: R306.1, U300.V10 (PMIC_CLKOUT); also elsewhere on the board
AOP_SPI_CLK: U300.D2 (SPIA_CLK); also elsewhere on the board
AOP_SPI_CS_N: U300.C2 (SPIA_CS_N); also elsewhere on the board
AOP_SPI_MISO: U300.D1 (SPIA_MISO); also elsewhere on the board
AOP_SPI_MOSI: U300.F2 (SPIA_MOSI); also elsewhere on the board
AOP_SYNC_IN: R313.1, U300.U12 (SYNC_IN); also elsewhere on the board
AOP_UART_RX: R314.1; also elsewhere on the board
AOP_UART_TX: U300.U16 (RS232_TX); also elsewhere on the board
FRAME_START: U300.K3 (GPIO_2); also elsewhere on the board
GND: C300.2, C301.2, C302.2, C303.2, C304.2, C305.2, C306.2, C307.2, C308.2, C309.2, C310.2, C311.2, C312.2, C313.2, C314.2, C315.2, C316.2, C317.2, C318.2, C319.2, C320.2, C321.2, C322.2, C323.2, C324.2, C325.2, C326.2, C327.2, C328.2, C329.2, C330.2, C331.2, C332.2, C333.2, C334.2, C335.2, C336.2, C337.2, C338.2, C339.2, C340.2, C341.2, C342.2, C343.2, C344.2, C345.2, C346.2, C347.2, C348.2, J301.3 (GND), J301.5 (GND), J301.9 (GNDDetect), R305.2, R306.2, R313.2, U300.A1 (VSS), U300.A2 (VSS), U300.A6 (VSSA), U300.A8 (VSSA), U300.A11 (VSSA), U300.A13 (VSSA), U300.A15 (VSSA), U300.A17 (VSSA), U300.A18 (VSSA), U300.B6 (VSSA), U300.B8 (VSSA), U300.B9 (VSSA), U300.B10 (VSSA), U300.B11 (VSSA), U300.B12 (VSSA), U300.B13 (VSSA), U300.B14 (VSSA), U300.B15 (VSSA), U300.B16 (VSSA), U300.B17 (VSSA), U300.B18 (VSSA), U300.C6 (VSSA), U300.C7 (VSSA), U300.C8 (VSSA), U300.C12 (VSSA), U300.C13 (VSSA), U300.C14 (VSSA), U300.C16 (VSSA), U300.C17 (VSSA), U300.D16 (VSSA), U300.D17 (VSSA), U300.D18 (VSSA), U300.E3 (VSS), U300.E16 (VSSA), U300.E17 (VSSA), U300.E18 (VSSA), U300.F3 (VSS), U300.F16 (VSSA), U300.F17 (VSSA), U300.F18 (VSSA), U300.K16 (VSSA), U300.K17 (VSSA), U300.K18 (VSSA), U300.L16 (VSSA), U300.L17 (VSSA), U300.L18 (VSSA), U300.N3 (VSS), U300.N16 (VSSA), U300.N17 (VSSA), U300.N18 (VSSA), U300.P3 (VSS), U300.P16 (VSSA), U300.R3 (VSS), U300.R16 (VSSA), U300.R17 (VSSA), U300.T4 (VSS), U300.T5 (VSS), U300.T6 (VSS), U300.T7 (VSS), U300.T8 (VSS), U300.T9 (VSS), U300.T10 (VSS), U300.T11 (VSS), U300.T12 (VSS), U300.T13 (VSS), U300.T14 (VSS), U300.T15 (VSS), U300.T16 (VSS), U300.T17 (VSSA), U300.U1 (VSS), U300.U17 (VSSA), U300.U18 (VSSA), U300.V1 (VSS), U300.V17 (VSSA), U300.V18 (VSSA), U301.4 (GND), Y300.2 (G), Y300.4 (G); also elsewhere on the board

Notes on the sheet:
SPIA pinmux 1; firmware 4-wire protocol. SYNC_IN: U12 mode1; pulse >25 ns, <4 us. R314 0R: remove for RX-ball isolation.
QE factory=0; verify SR bit6=1. Wait WIP=0 before reset (MSS#45).
CL=12pF; 18pF + stray. Tune loading / drive.
LVDS off (ANA#16); VPP NC. Unused digital/analog pins NC. FRAME_START: K3 mode13. UARTA RX/TX: V16/U16 mode2/5. UARTB TX: E2 mode6.
C301..311: 100nF / ball; short BGA returns.
Before MMWave_open(): ldoBypassEnable=3. ioSupplyIndicator=0; supplyMonIrDrop from PCB. 0.95..1.05V at balls; qualify ripple + IR drop.
C345 47nF (ANA#19); A9/A10 decouple only. E-plane gaps 0.2mm; keep aperture clear of metal.
RADAR / UART / SPIA
QSPI / STRAPS / 40 MHz / JTAG
RESERVED / GROUND BALLS
1V2 DIGITAL / SRAM
1V8 ANALOG
1V0 RF / PA
3V3 I/O
REFERENCE OUTPUTS
1V8 valid before 3V3 (MSS#38A). Carrier Hi-Z while 3V3_R is off.
